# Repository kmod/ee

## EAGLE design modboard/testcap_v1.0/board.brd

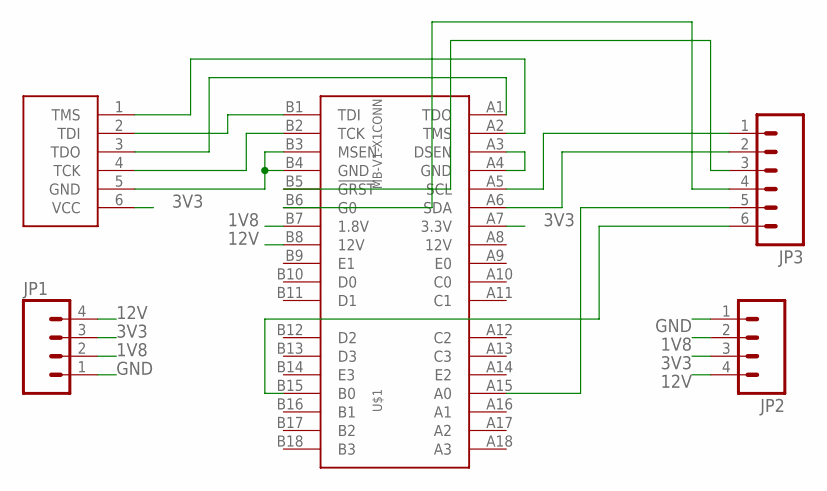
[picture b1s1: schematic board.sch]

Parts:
JP1, JP2: M04PTH; 1X04
JP3: M06SIP; 1X06
U$1: MB-V1-X1CONN; PCIE-X1-CONN
U$2: JTAGDIGILENT; 1X06

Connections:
1V8: JP1.2, JP2.2, U$1.B7 (1.8V)
3V3: JP1.3, JP2.3, U$1.A7 (3.3V), U$2.6 (VCC)
12V: JP1.4, JP2.4, U$1.B8 (12V)
A0: JP3.5, U$1.A15 (A0)
B0: JP3.6, U$1.B15 (B0)
G0: JP3.4, U$1.B6 (G0)
GND: JP1.1, JP2.1, U$1.B3 (MSEN), U$1.B4 (GND), U$2.5 (GND)
GRST: JP3.3, U$1.B5 (!GRST)
unnamed: U$1.A3 (DSEN), U$1.A4 (GND)
SCL: JP3.1, U$1.A5 (SCL)
SDA: JP3.2, U$1.A6 (SDA)
TCK: U$1.B2 (TCK), U$2.4 (TCK)
TDI: U$1.B1 (TDI), U$2.2 (TDI)
TDO: U$1.A1 (TDO), U$2.3 (TDO)
TMS: U$1.A2 (TMS), U$2.1 (TMS)

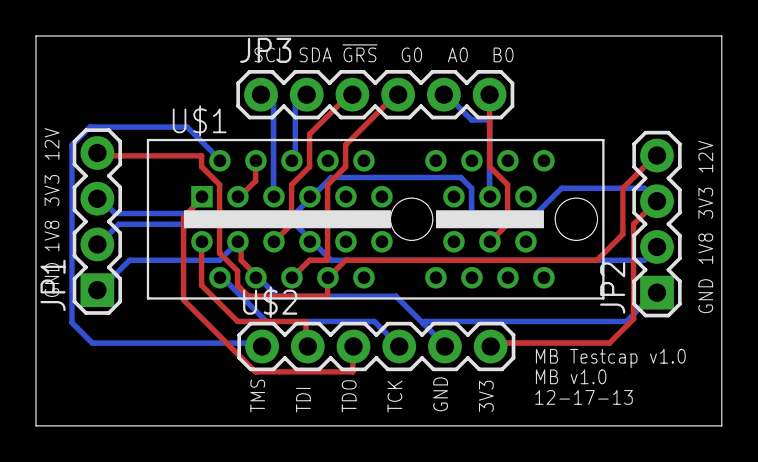
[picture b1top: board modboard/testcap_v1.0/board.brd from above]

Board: 2 copper layers, 38.1 x 21.7 mm, 5 parts (0 on the bottom side), 15 nets.

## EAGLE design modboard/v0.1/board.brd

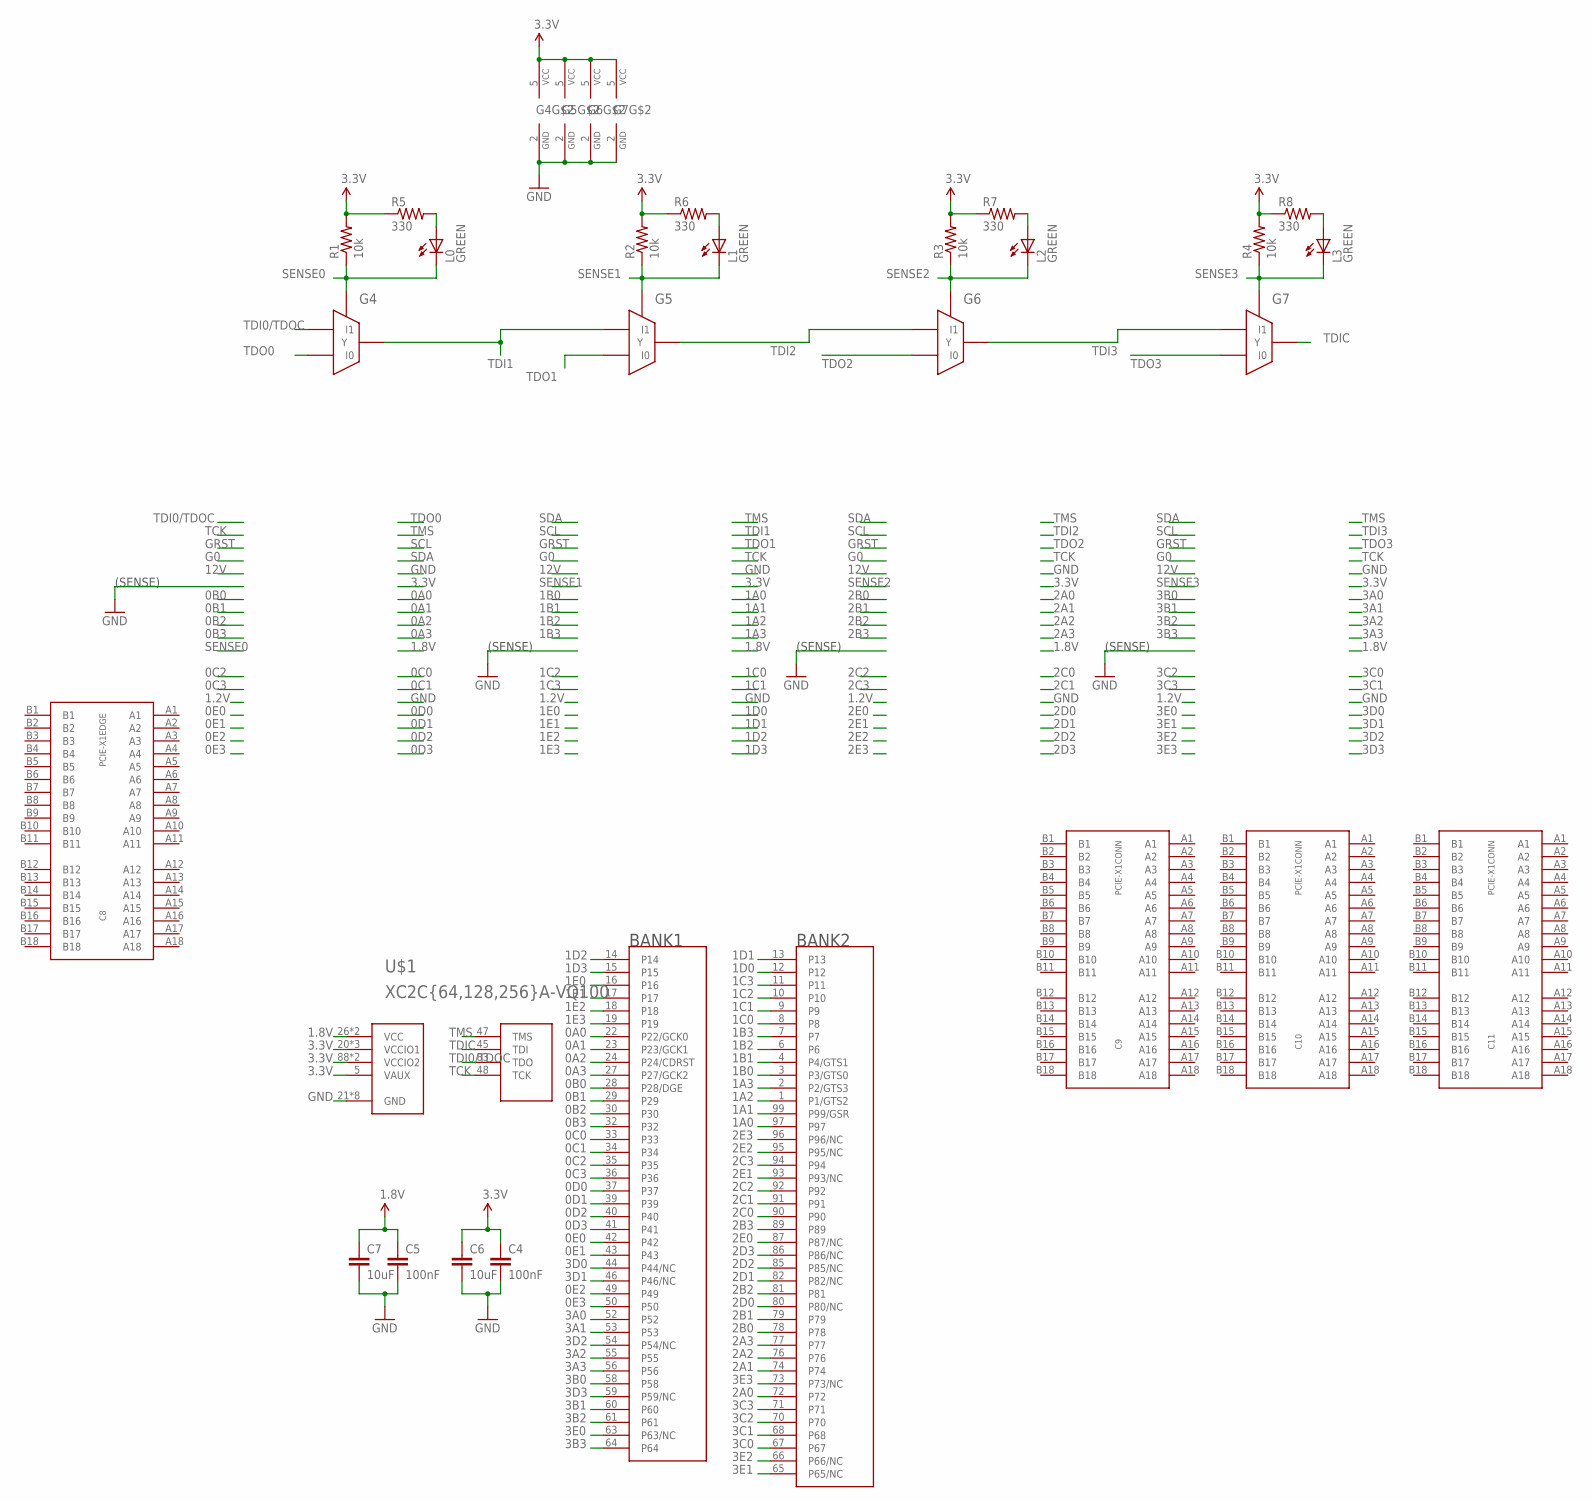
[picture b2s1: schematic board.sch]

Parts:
C4, C5: 100nF; 0402-CAP
C6, C7: 10uF; 0805
C8: PCIE-X1EDGE; PCIE-X1-EDGE
C9, C10, C11: PCIE-X1CONN; PCIE-X1-CONN
G4, G5, G6, G7: 74G157; SOT363
L0, L1, L2, L3: GREEN; 0603_LED
R1, R2, R3, R4: 10k; 0603-RES
R5, R6, R7, R8: 330; 0603-RES
U$1: XC2C{64,128,256}A-VQ100; XILINX_TQ100

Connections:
0A0: U$1.22 (P22/GCK0)
0A1: U$1.23 (P23/GCK1)
0A2: U$1.24 (P24/CDRST)
0A3: U$1.27 (P27/GCK2)
0B0: U$1.28 (P28/DGE)
0B1: U$1.29
0B2: U$1.30
0B3: U$1.32
0C0: U$1.33
0C1: U$1.34
0C2: U$1.35
0C3: U$1.36
0D0: U$1.37
0D1: U$1.39
0D2: U$1.40
0D3: U$1.41
0E0: U$1.42
0E1: U$1.43
0E2: U$1.49
0E3: U$1.50
1.8V: C5.1, C7.1, U$1.26 (VCC), U$1.57 (VCC)
1A0: U$1.97
1A1: U$1.99 (P99/GSR)
1A2: U$1.1 (P1/GTS2)
1A3: U$1.2 (P2/GTS3)
1B0: U$1.3 (P3/GTS0)
1B1: U$1.4 (P4/GTS1)
1B2: U$1.6
1B3: U$1.7
1C0: U$1.8
1C1: U$1.9
1C2: U$1.10
1C3: U$1.11
1D0: U$1.12
1D1: U$1.13
1D2: U$1.14
1D3: U$1.15
1E0: U$1.16
1E1: U$1.17
1E2: U$1.18
1E3: U$1.19
2A0: U$1.72
2A1: U$1.74
2A2: U$1.76
2A3: U$1.77
2B0: U$1.78
2B1: U$1.79
2B2: U$1.81
2B3: U$1.89
2C0: U$1.90
2C1: U$1.91
2C2: U$1.92
2C3: U$1.94
2D0: U$1.80 (P80/NC)
2D1: U$1.82 (P82/NC)
2D2: U$1.85 (P85/NC)
2D3: U$1.86 (P86/NC)
2E0: U$1.87 (P87/NC)
2E1: U$1.93 (P93/NC)
2E2: U$1.95 (P95/NC)
2E3: U$1.96 (P96/NC)
3.3V: C4.1, C6.1, G4.5 (VCC), G5.5 (VCC), G6.5 (VCC), G7.5 (VCC), R1.2, R2.2, R3.2, R4.2, R5.1, R6.1, R7.1, R8.1, U$1.5 (VAUX), U$1.20 (VCCIO1), U$1.38 (VCCIO1), U$1.51 (VCCIO1), U$1.88 (VCCIO2), U$1.98 (VCCIO2)
3A0: U$1.52
3A1: U$1.53
3A2: U$1.55
3A3: U$1.56
3B0: U$1.58
3B1: U$1.60
3B2: U$1.61
3B3: U$1.64
3C0: U$1.67
3C1: U$1.68
3C2: U$1.70
3C3: U$1.71
3D0: U$1.44 (P44/NC)
3D1: U$1.46 (P46/NC)
3D2: U$1.54 (P54/NC)
3D3: U$1.59 (P59/NC)
3E0: U$1.63 (P63/NC)
3E1: U$1.65 (P65/NC)
3E2: U$1.66 (P66/NC)
3E3: U$1.73 (P73/NC)
GND: C4.2, C5.2, C6.2, C7.2, G4.2 (GND), G5.2 (GND), G6.2 (GND), G7.2 (GND), U$1.21 (GND), U$1.25 (GND), U$1.31 (GND), U$1.62 (GND), U$1.69 (GND), U$1.75 (GND), U$1.84 (GND), U$1.100 (GND)
unnamed: L0.A, R5.2
unnamed: L1.A, R6.2
unnamed: L2.A, R7.2
unnamed: L3.A, R8.2
SENSE0: G4.6 (S), L0.C, R1.1
SENSE1: G5.6 (S), L1.C, R2.1
SENSE2: G6.6 (S), L2.C, R3.1
SENSE3: G7.6 (S), L3.C, R4.1
TCK: U$1.48 (TCK)
TDI0/TDOC: G4.1 (I1), U$1.83 (TDO)
TDI1: G4.4 (Y), G5.1 (I1)
TDI2: G5.4 (Y), G6.1 (I1)
TDI3: G6.4 (Y), G7.1 (I1)
TDIC: G7.4 (Y), U$1.45 (TDI)
TDO0: G4.3 (I0)
TDO1: G5.3 (I0)
TDO2: G6.3 (I0)
TDO3: G7.3 (I0)
TMS: U$1.47 (TMS)

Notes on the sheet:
(SENSE)

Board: 2 copper layers, 25 parts (4 on the bottom side), 16 nets, no tracks yet.

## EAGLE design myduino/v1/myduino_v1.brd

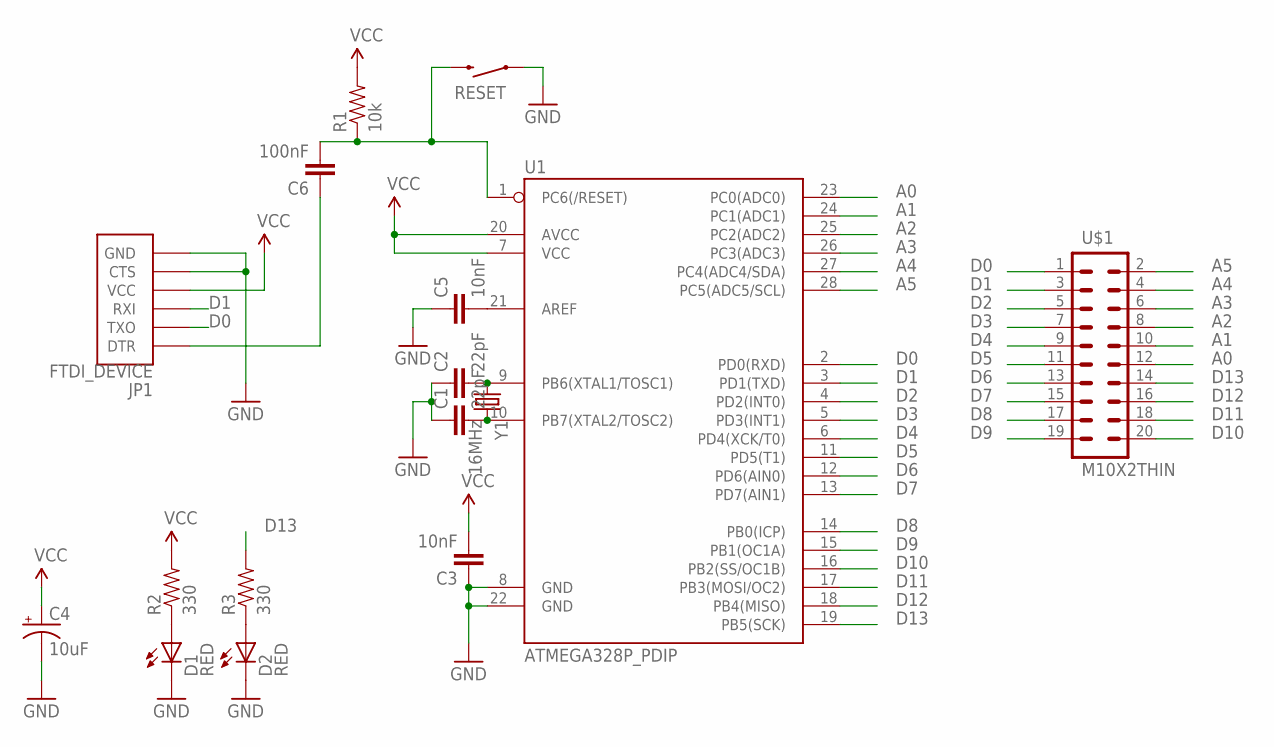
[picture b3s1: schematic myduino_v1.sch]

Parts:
C1, C2: 22pF; 0402-CAP
C3, C5: 10nF; 0402-CAP
C4: 10uF; EIA3216
C6: 100nF; 0402-CAP
D1, D2: RED; LED-0603
JP1: FTDI_DEVICE; FTDI_DEVICE_SIDE
R1: 10k; 0603-RES
R2, R3: 330; 0603-RES
RESET: SWITCH-MOMENTARY-2PTH; TACTILE-PTH
U1: ATMEGA328P_PDIP; DIL28-3
U$1: M10X2THIN; 2X10_THIN
Y1: 16MHz; HC49US

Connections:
A0: U1.23 (PC0(ADC0)), U$1.12
A1: U1.24 (PC1(ADC1)), U$1.10
A2: U1.25 (PC2(ADC2)), U$1.8
A3: U1.26 (PC3(ADC3)), U$1.6
A4: U1.27 (PC4(ADC4/SDA)), U$1.4
A5: U1.28 (PC5(ADC5/SCL)), U$1.2
D0: JP1.P$2 (TXO), U1.2 (PD0(RXD)), U$1.1
D1: JP1.P$3 (RXI), U1.3 (PD1(TXD)), U$1.3
D2: U1.4 (PD2(INT0)), U$1.5
D3: U1.5 (PD3(INT1)), U$1.7
D4: U1.6 (PD4(XCK/T0)), U$1.9
D5: U1.11 (PD5(T1)), U$1.11
D6: U1.12 (PD6(AIN0)), U$1.13
D7: U1.13 (PD7(AIN1)), U$1.15
D8: U1.14 (PB0(ICP)), U$1.17
D9: U1.15 (PB1(OC1A)), U$1.19
D10: U1.16 (PB2(SS/OC1B)), U$1.20
D11: U1.17 (PB3(MOSI/OC2)), U$1.18
D12: U1.18 (PB4(MISO)), U$1.16
D13: R3.2, U1.19 (PB5(SCK)), U$1.14
GND: C1.1, C2.1, C3.1, C4.C (-), C5.1, D1.C, D2.C, JP1.P$5 (CTS), JP1.P$6 (GND), RESET.1, U1.8 (GND), U1.22 (GND)
unnamed: D2.A, R3.1
unnamed: C1.2, U1.10 (PB7(XTAL2/TOSC2)), Y1.2
unnamed: C2.2, U1.9 (PB6(XTAL1/TOSC1)), Y1.1
unnamed: C5.2, U1.21 (AREF)
unnamed: C6.2, R1.1, RESET.3 (2), U1.1 (PC6(/RESET))
unnamed: D1.A, R2.1
unnamed: C6.1, JP1.P$1 (DTR)
VCC: C3.2, C4.A (+), JP1.P$4 (VCC), R1.2, R2.2, U1.7 (VCC), U1.20 (AVCC)

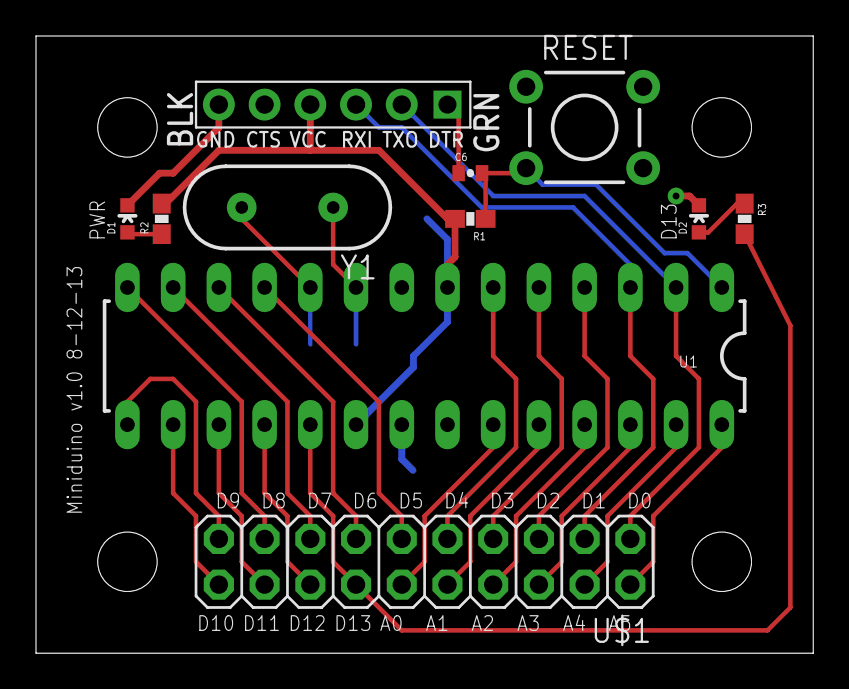
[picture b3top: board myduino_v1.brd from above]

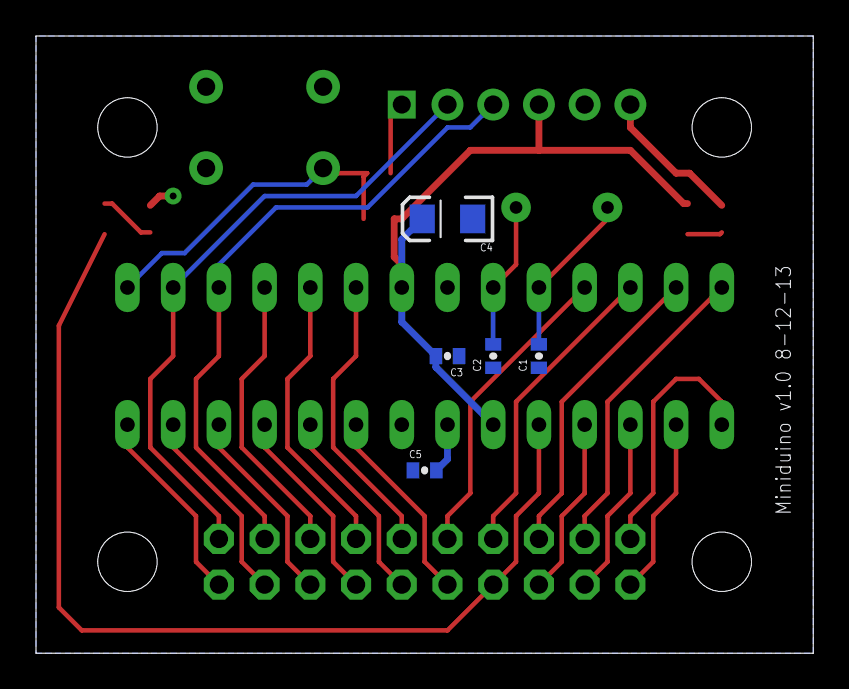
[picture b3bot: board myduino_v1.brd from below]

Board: 2 copper layers, 43.2 x 34.3 mm, 20 parts (5 on the bottom side), 29 nets.

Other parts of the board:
U$2, U$3, U$4, U$5: STAND-OFF

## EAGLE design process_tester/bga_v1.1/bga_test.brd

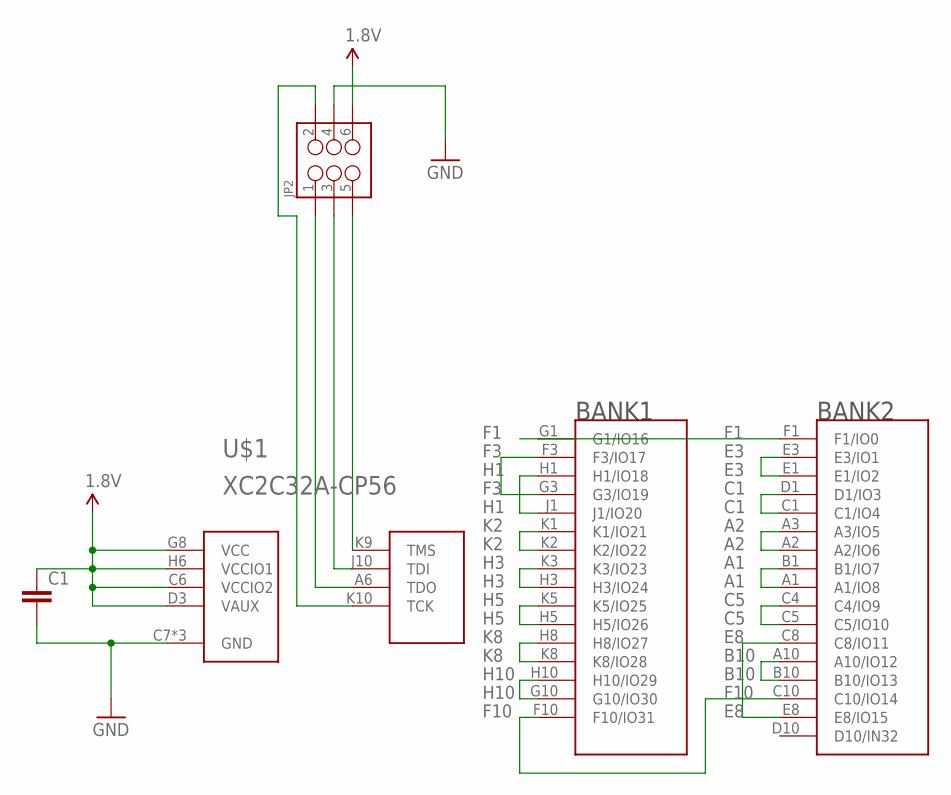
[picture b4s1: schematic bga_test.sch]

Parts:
C1: CAP0402-CAP; 0402-CAP
JP2: M03X2NO_SILK; 2X3-NS
U$1: XC2C32A-CP56; XILINX_CP56

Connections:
1.8V: C1.1, JP2.6, U$1.C6 (VCCIO2), U$1.D3 (VAUX), U$1.G8 (VCC), U$1.H6 (VCCIO1)
A1: U$1.A1 (A1/IO8), U$1.B1 (B1/IO7)
A2: U$1.A2 (A2/IO6), U$1.A3 (A3/IO5)
B10: U$1.A10 (A10/IO12), U$1.B10 (B10/IO13)
C1: U$1.C1 (C1/IO4), U$1.D1 (D1/IO3)
C5: U$1.C4 (C4/IO9), U$1.C5 (C5/IO10)
E3: U$1.E1 (E1/IO2), U$1.E3 (E3/IO1)
E8: U$1.C8 (C8/IO11), U$1.E8 (E8/IO15)
F1: U$1.F1 (F1/IO0), U$1.G1 (G1/IO16)
F3: U$1.F3 (F3/IO17), U$1.G3 (G3/IO19)
F10: U$1.C10 (C10/IO14), U$1.F10 (F10/IO31)
GND: C1.2, JP2.4, U$1.C7 (GND), U$1.F8 (GND), U$1.H4 (GND)
H1: U$1.H1 (H1/IO18), U$1.J1 (J1/IO20)
H3: U$1.H3 (H3/IO24), U$1.K3 (K3/IO23)
H5: U$1.H5 (H5/IO26), U$1.K5 (K5/IO25)
H10: U$1.G10 (G10/IO30), U$1.H10 (H10/IO29)
K2: U$1.K1 (K1/IO21), U$1.K2 (K2/IO22)
K8: U$1.H8 (H8/IO27), U$1.K8 (K8/IO28)
TCK: JP2.2, U$1.K10 (TCK)
TDI: JP2.3, U$1.J10 (TDI)
TDO: JP2.1, U$1.A6 (TDO)
TMS: JP2.5, U$1.K9 (TMS)

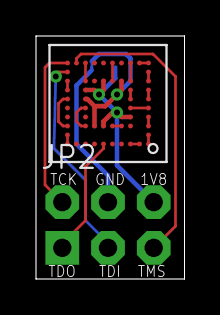
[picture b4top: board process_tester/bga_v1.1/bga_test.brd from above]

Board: 2 copper layers, 8.2 x 13.5 mm, 3 parts (1 on the bottom side), 22 nets.

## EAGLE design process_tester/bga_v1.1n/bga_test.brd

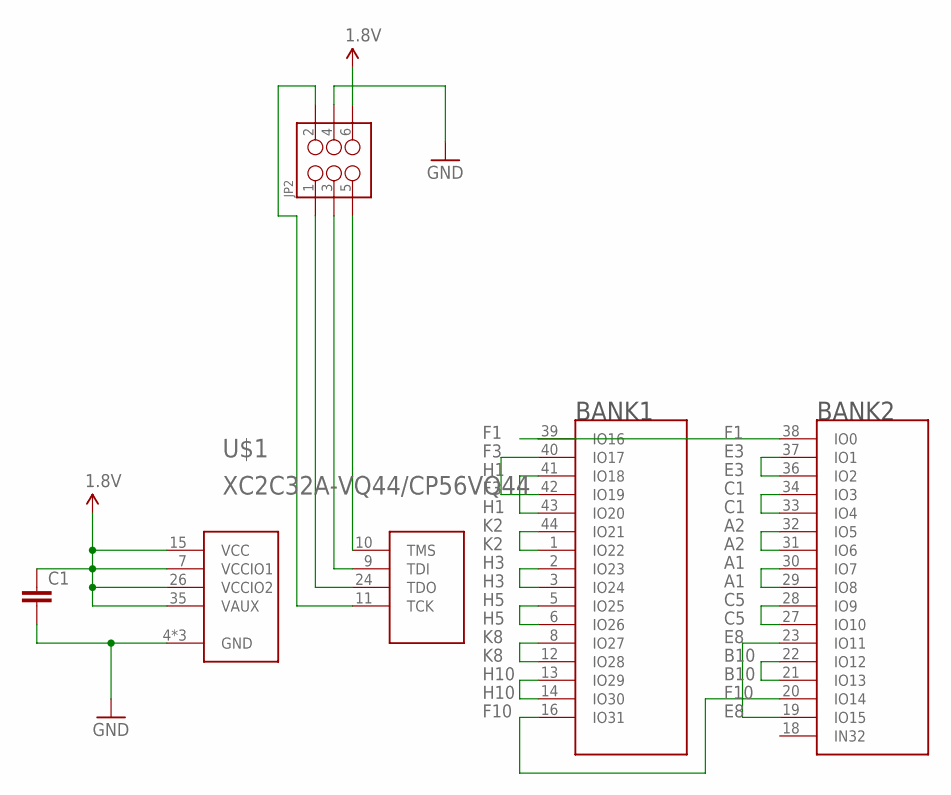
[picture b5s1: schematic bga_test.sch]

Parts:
C1: CAP0402-CAP; 0402-CAP
JP2: M03X2NO_SILK; 2X3-NS
U$1: XC2C32A-VQ44/CP56VQ44; XILINX_VQ44

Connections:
1.8V: C1.1, JP2.6, U$1.7 (VCCIO1), U$1.15 (VCC), U$1.26 (VCCIO2), U$1.35 (VAUX)
A1: U$1.29 (IO8), U$1.30 (IO7)
A2: U$1.31 (IO6), U$1.32 (IO5)
B10: U$1.21 (IO13), U$1.22 (IO12)
C1: U$1.33 (IO4), U$1.34 (IO3)
C5: U$1.27 (IO10), U$1.28 (IO9)
E3: U$1.36 (IO2), U$1.37 (IO1)
E8: U$1.19 (IO15), U$1.23 (IO11)
F1: U$1.38 (IO0), U$1.39 (IO16)
F3: U$1.40 (IO17), U$1.42 (IO19)
F10: U$1.16 (IO31), U$1.20 (IO14)
GND: C1.2, JP2.4, U$1.4 (GND), U$1.17 (GND), U$1.25 (GND)
H1: U$1.41 (IO18), U$1.43 (IO20)
H3: U$1.2 (IO23), U$1.3 (IO24)
H5: U$1.5 (IO25), U$1.6 (IO26)
H10: U$1.13 (IO29), U$1.14 (IO30)
K2: U$1.1 (IO22), U$1.44 (IO21)
K8: U$1.8 (IO27), U$1.12 (IO28)
TCK: JP2.2, U$1.11 (TCK)
TDI: JP2.3, U$1.9 (TDI)
TDO: JP2.1, U$1.24 (TDO)
TMS: JP2.5, U$1.10 (TMS)

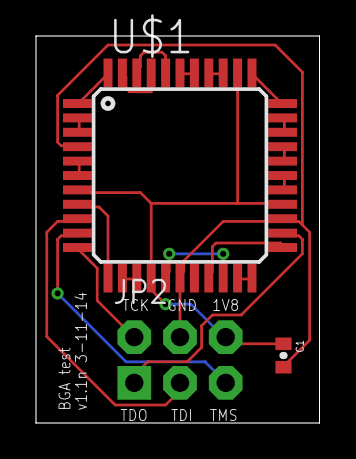
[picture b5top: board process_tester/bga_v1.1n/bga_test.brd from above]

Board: 2 copper layers, 15.8 x 21.5 mm, 3 parts (0 on the bottom side), 22 nets.

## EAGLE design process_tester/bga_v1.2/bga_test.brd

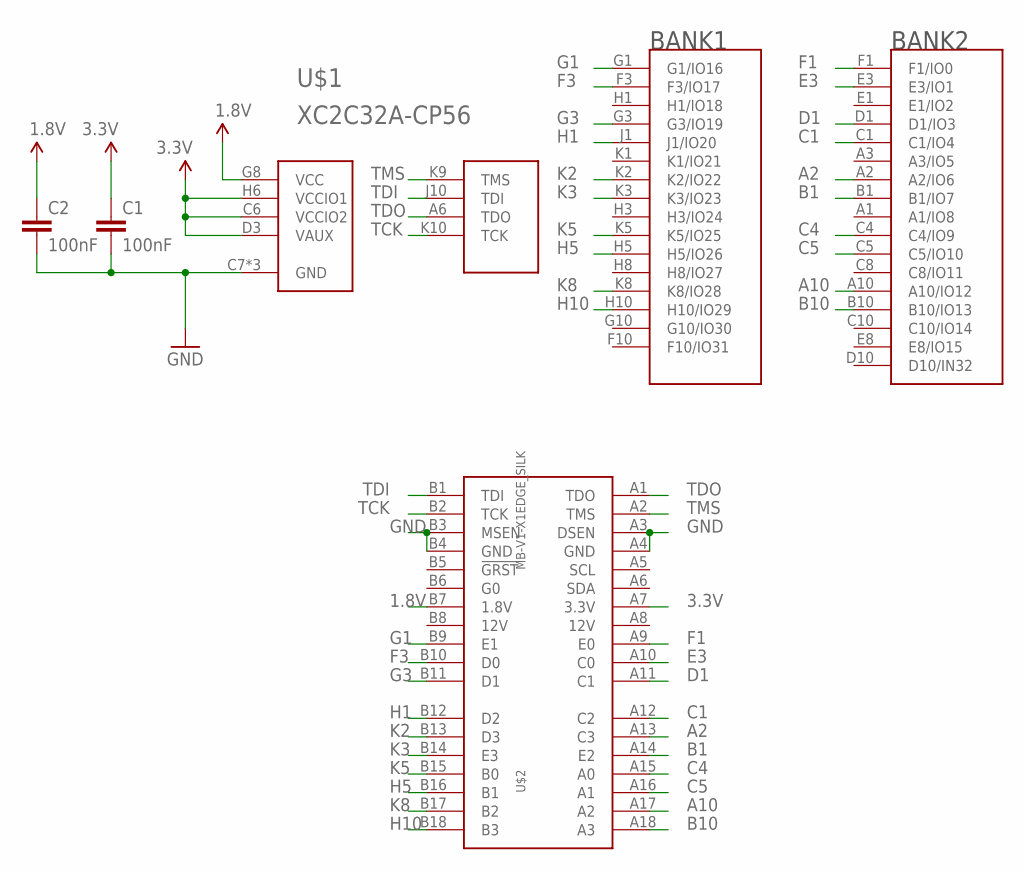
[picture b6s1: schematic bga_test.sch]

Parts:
C1, C2: 100nF; 0402-CAP
U$1: XC2C32A-CP56; XILINX_CP56
U$2: MB-V1-X1EDGE_SILK; MB-V1-X1-EDGE

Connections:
1.8V: C2.1, U$1.G8 (VCC), U$2.B7 (1.8V)
3.3V: C1.1, U$1.C6 (VCCIO2), U$1.D3 (VAUX), U$1.H6 (VCCIO1), U$2.A7 (3.3V)
A2: U$1.A2 (A2/IO6), U$2.A13 (C3)
A10: U$1.A10 (A10/IO12), U$2.A17 (A2)
B1: U$1.B1 (B1/IO7), U$2.A14 (E2)
B10: U$1.B10 (B10/IO13), U$2.A18 (A3)
C1: U$1.C1 (C1/IO4), U$2.A12 (C2)
C4: U$1.C4 (C4/IO9), U$2.A15 (A0)
C5: U$1.C5 (C5/IO10), U$2.A16 (A1)
D1: U$1.D1 (D1/IO3), U$2.A11 (C1)
E3: U$1.E3 (E3/IO1), U$2.A10 (C0)
F1: U$1.F1 (F1/IO0), U$2.A9 (E0)
F3: U$1.F3 (F3/IO17), U$2.B10 (D0)
G1: U$1.G1 (G1/IO16), U$2.B9 (E1)
G3: U$1.G3 (G3/IO19), U$2.B11 (D1)
GND: C1.2, C2.2, U$1.C7 (GND), U$1.F8 (GND), U$1.H4 (GND), U$2.A3 (DSEN), U$2.A4 (GND), U$2.B3 (MSEN), U$2.B4 (GND)
H1: U$1.J1 (J1/IO20), U$2.B12 (D2)
H5: U$1.H5 (H5/IO26), U$2.B16 (B1)
H10: U$1.H10 (H10/IO29), U$2.B18 (B3)
K2: U$1.K2 (K2/IO22), U$2.B13 (D3)
K3: U$1.K3 (K3/IO23), U$2.B14 (E3)
K5: U$1.K5 (K5/IO25), U$2.B15 (B0)
K8: U$1.K8 (K8/IO28), U$2.B17 (B2)
TCK: U$1.K10 (TCK), U$2.B2 (TCK)
TDI: U$1.J10 (TDI), U$2.B1 (TDI)
TDO: U$1.A6 (TDO), U$2.A1 (TDO)
TMS: U$1.K9 (TMS), U$2.A2 (TMS)

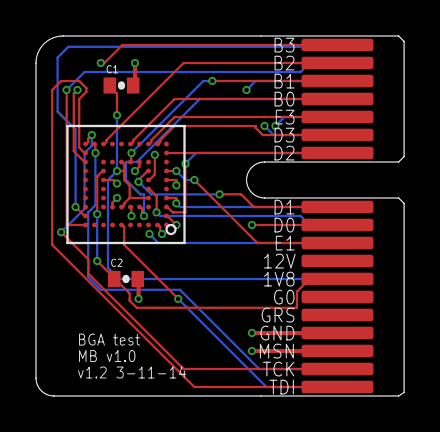
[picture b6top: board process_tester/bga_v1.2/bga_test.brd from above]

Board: 4 copper layers, 20.4 x 20.0 mm, 4 parts (0 on the bottom side), 27 nets.

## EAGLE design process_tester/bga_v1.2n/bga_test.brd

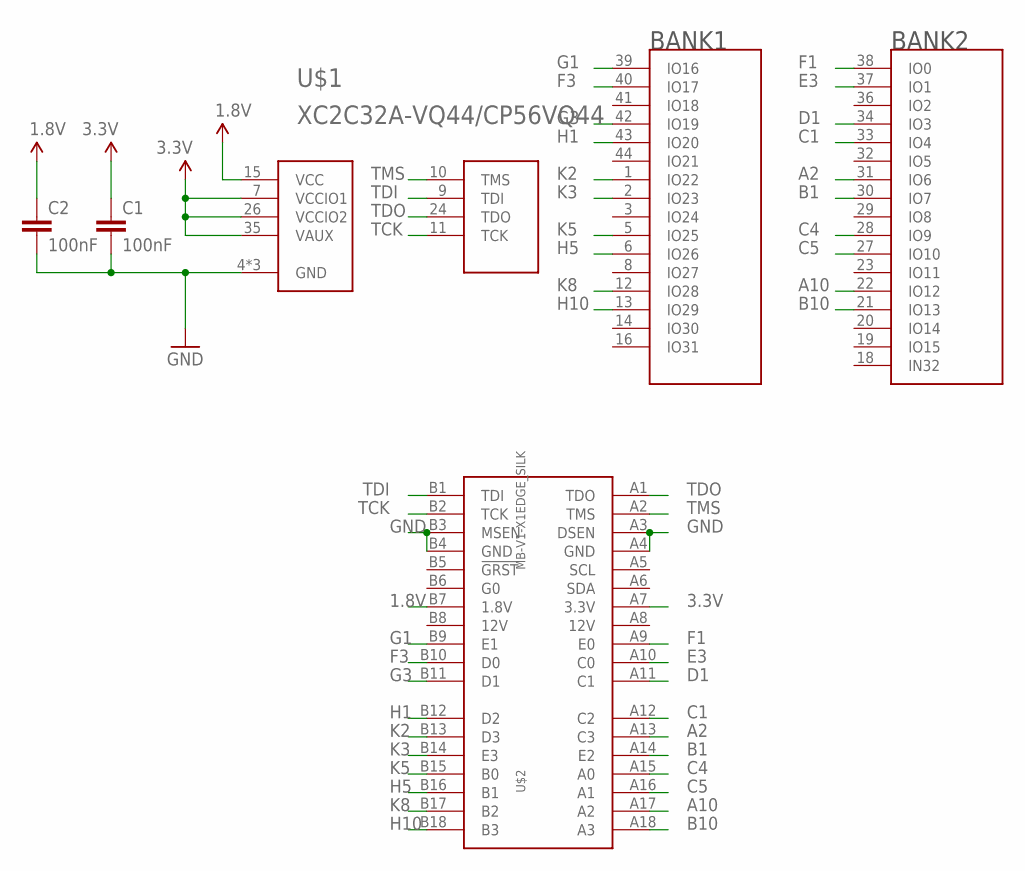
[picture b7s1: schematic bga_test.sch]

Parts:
C1, C2: 100nF; 0402-CAP
U$1: XC2C32A-VQ44/CP56VQ44; XILINX_VQ44
U$2: MB-V1-X1EDGE_SILK; MB-V1-X1-EDGE

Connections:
1.8V: C2.1, U$1.15 (VCC), U$2.B7 (1.8V)
3.3V: C1.1, U$1.7 (VCCIO1), U$1.26 (VCCIO2), U$1.35 (VAUX), U$2.A7 (3.3V)
A2: U$1.31 (IO6), U$2.A13 (C3)
A10: U$1.22 (IO12), U$2.A17 (A2)
B1: U$1.30 (IO7), U$2.A14 (E2)
B10: U$1.21 (IO13), U$2.A18 (A3)
C1: U$1.33 (IO4), U$2.A12 (C2)
C4: U$1.28 (IO9), U$2.A15 (A0)
C5: U$1.27 (IO10), U$2.A16 (A1)
D1: U$1.34 (IO3), U$2.A11 (C1)
E3: U$1.37 (IO1), U$2.A10 (C0)
F1: U$1.38 (IO0), U$2.A9 (E0)
F3: U$1.40 (IO17), U$2.B10 (D0)
G1: U$1.39 (IO16), U$2.B9 (E1)
G3: U$1.42 (IO19), U$2.B11 (D1)
GND: C1.2, C2.2, U$1.4 (GND), U$1.17 (GND), U$1.25 (GND), U$2.A3 (DSEN), U$2.A4 (GND), U$2.B3 (MSEN), U$2.B4 (GND)
H1: U$1.43 (IO20), U$2.B12 (D2)
H5: U$1.6 (IO26), U$2.B16 (B1)
H10: U$1.13 (IO29), U$2.B18 (B3)
K2: U$1.1 (IO22), U$2.B13 (D3)
K3: U$1.2 (IO23), U$2.B14 (E3)
K5: U$1.5 (IO25), U$2.B15 (B0)
K8: U$1.12 (IO28), U$2.B17 (B2)
TCK: U$1.11 (TCK), U$2.B2 (TCK)
TDI: U$1.9 (TDI), U$2.B1 (TDI)
TDO: U$1.24 (TDO), U$2.A1 (TDO)
TMS: U$1.10 (TMS), U$2.A2 (TMS)

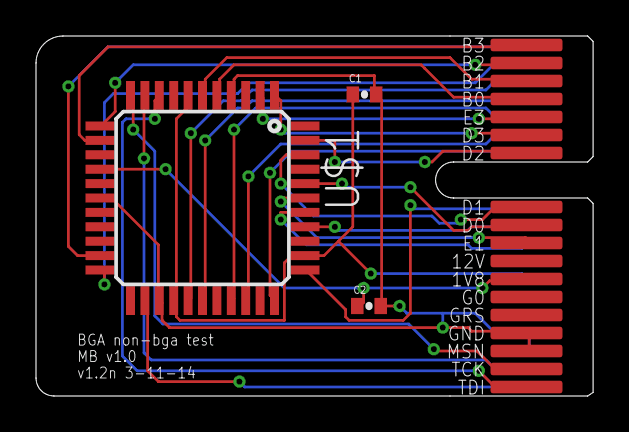
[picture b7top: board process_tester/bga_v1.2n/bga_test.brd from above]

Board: 2 copper layers, 30.9 x 20.0 mm, 4 parts (0 on the bottom side), 27 nets.

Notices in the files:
parts and their libraries:
SparkFun-DiscreteSemi: Licensing: Creative Commons ShareAlike 4.0 International - https://creativecommons.org/licenses/by-sa/4.0
SparkFun-Aesthetics: Licensing: CC v3.0 Share-Alike You are welcome to use this library for commercial purposes.
